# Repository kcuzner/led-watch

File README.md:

# LED Wristwatch

By Kevin Cuzner

## Design Features

- 32mm PCB diameter utilizing 72 0603 LEDs as the primary time display
    - Target is 3 square inches, 4 layer, with standard technology (6mil trace,
      no via in pad, etc)
- 100mAH battery from [PowerStream](http://www.powerstream.com/)
- Very high efficiency buck regulator.
    - Target battery life: >168 hours
- USB charging
- STM32L0-series microcontroller
- Side-actuated mid-board PCB mount buttons with an option for replacement with
  capacitive sensors.

## Key components

 - STM32L052C8 ultra-low power microcontroller
 - MMA8652 accelerometer
 - TPS65736 ultra-low quiescent current buck regulator
 - MCP73832 Li-Ion charge management controller

## Current status

This project is fairly complete, though the bootloader is still a work in
progress and may never be completed. The board was built and everything worked
after adding some reworks:

 - Trace to 3.3V from the SCL pullup was missing on the PCB. Apparently I
   deleted it while shuffling resistors around and didn't notice.
 - Central LED footprint was flipped across the X axis. The fix was to remove
   R35, short pins 1 and 4, and give up on having a blue LED in the center.
 - Leakage on Q1 through R4 (and D2, D1, and possibly U1) was enough to turn on
   the transistor. Changed R4 to 20K and bodged in a 4.7K resistor between Q1
   pins 1 and 2.

There were also two part issues which were resolved in software mostly:

 - The buttons I chose are extremely fragile. The mere act of inserting the PCB
   into the case put enough strain on them at times that 3 of the 4 buttons
   ended up breaking (they were constructed of a plastic housing with a metal
   dome held in place with what appears to be kapton tape). The buttons were
   simply not used in the software.
 - The blue LEDs I chose did not have a reverse current specification and in
   fact were not designed for reverse voltage operation. I didn't notice this
   when choosing parts, as I was rather focused on the forward voltage.
   Considering that reverse voltage is kind of key to the design here, that
   didn't work so well. Combined, the blue LEDs would draw about 28mA when the
   watch face was on or off because they actually conduct backwards. It could be
   said that they have an extremely high reverse leakage current, but I'm sure
   there's more going on there. The fix for this was to ensure that pin PA5,
   which drives the blue LEDs, was always high when the mux was disabled and all
   of its pins were driven high (effectively putting 0V across the LEDs). This
   does not reduce current consumption when the display is running (it still
   draws around 28mA), but it did reduce the sleep current to about 0.47mA.

Currently, the only method of input is either through USB or through the
accelerometer. The time is set through USB to the current time on the host PC.
The watch will automatically sleep when it is removed from USB power and will
wake when the accelerometer is tapped. When the watch is awake, the current time
is displayed. It currently stays on for about 15 seconds until shutting off
again. When USB power is reapplied the watch will reawaken. The future plans are
to also enable USB programmability of the watch, though this may never be
completed depending on my schedule and level of interest. The buttons may never
be used because they are so easy to break, but the idea was to have it behave
like a real digital watch with a timer and everything. All it does with the
buttons right now is beep when they are pressed.

As this is my first complete hardware design that I am releasing like this, I do
reserve the right to take it down at any time. I'm releasing it in the hopes
that someone finds it useful, though it clearly has its own problems and
shouldn't be considered as a reference design.

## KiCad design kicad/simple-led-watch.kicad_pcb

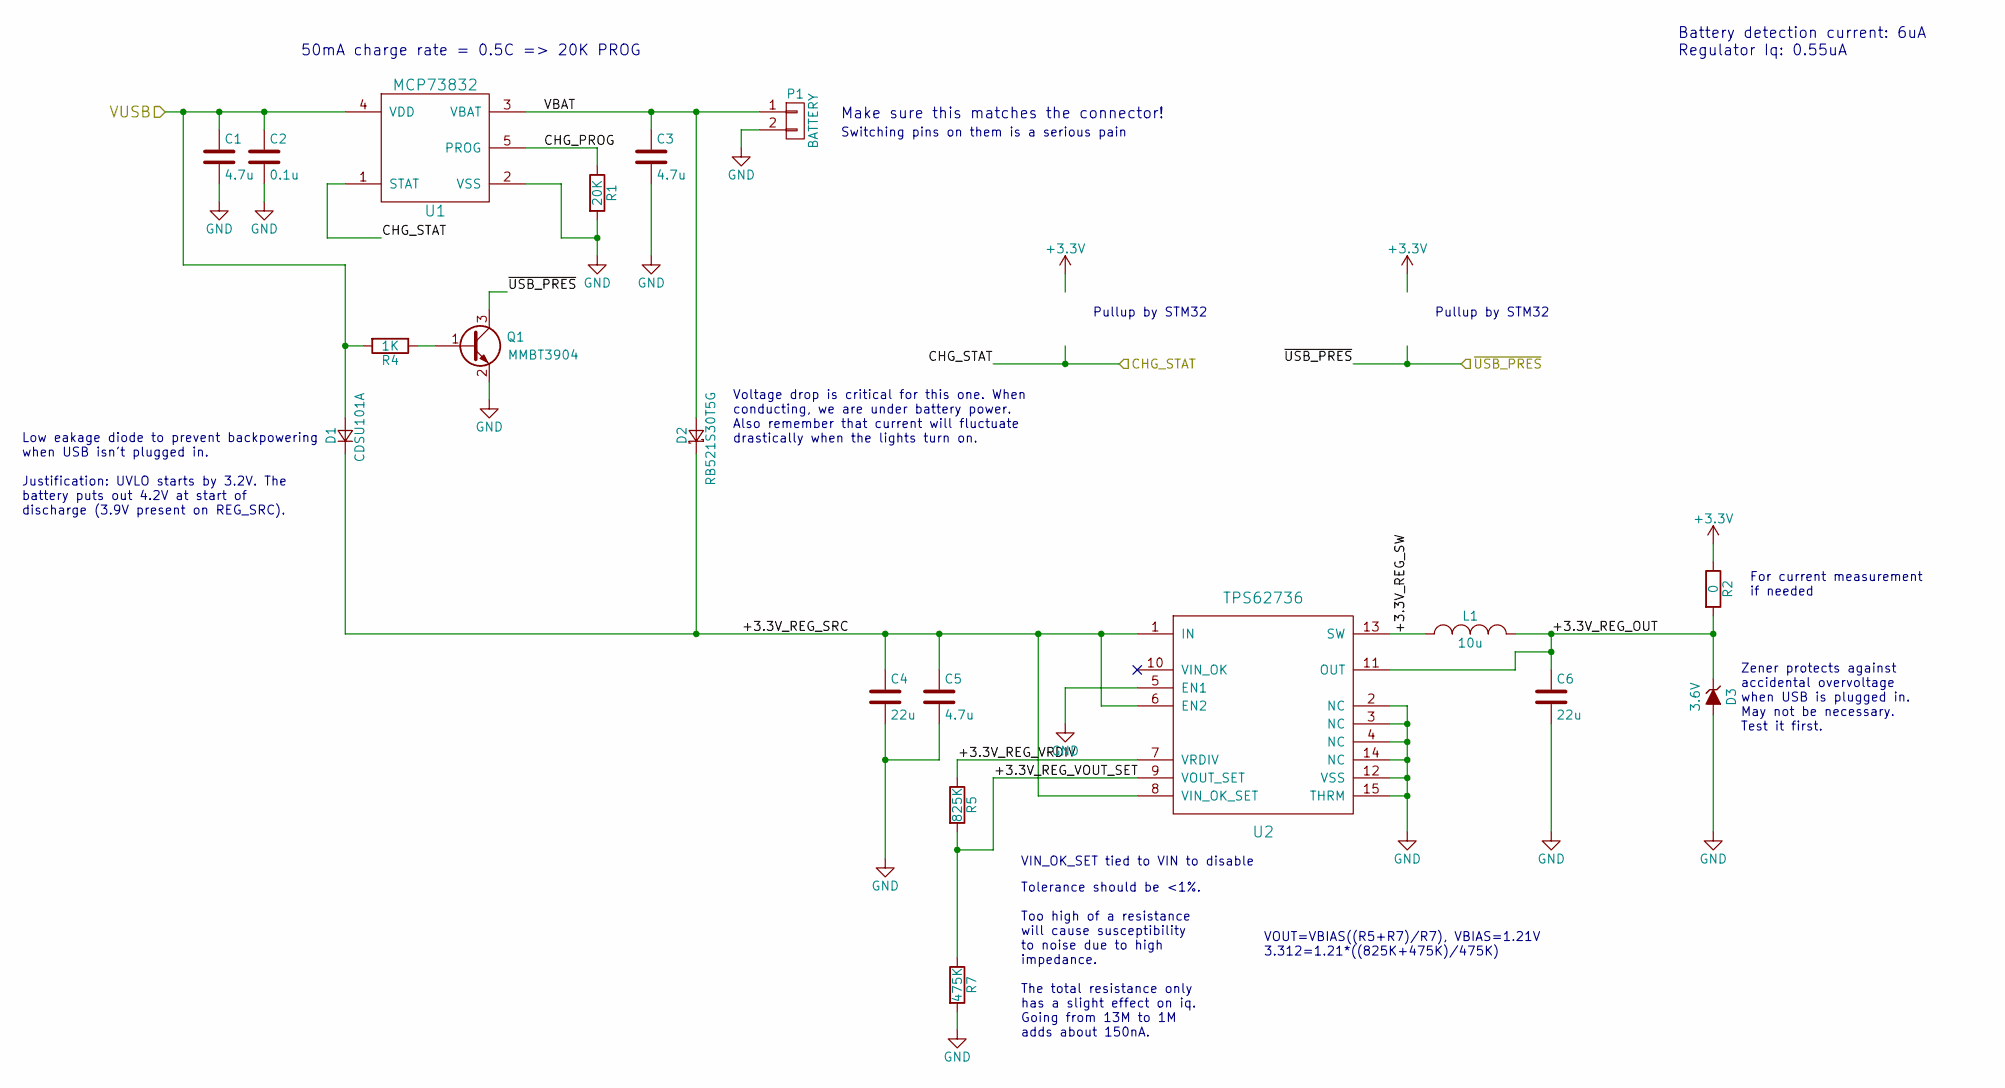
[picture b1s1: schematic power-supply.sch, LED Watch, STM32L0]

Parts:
C1, C3, C5: 4.7u; C_0402; Part No. 1276-6819-1-ND
C2: 0.1u; C_0402; Part No. 1276-1022-1-ND
C4, C6: 22u; C_0603; Part No. 1276-6504-1-ND
D1: CDSU101A; SOD-523; Part No. 641-1002-1-ND
D2: RB521S30T5G; SOD-523; Part No. RB521S30T5GOSCT-ND
D3: 3.6V; SOD-523; Part No. DZ2S036M0LCT-ND
L1: 10u; SMD_1008; Part No. 490-10563-1-ND
P1: BATTERY; JST-ACH-2PIN; Part No. 455-2202-1-ND
Q1: MMBT3904; SOT-23; Part No. MMBT3904FSCT-ND
R1: 20K; R_0402; Part No. 311-20.0KLRCT-ND
R2: 0; R_0402; Part No. 311-0.0JRCT-ND
R4: 1K; R_0402; Part No. 311-1.00KLRCT-ND
R5: 825K; R_0402; Part No. YAG3241CT-ND
R7: 475K; R_0402; Part No. 311-475KLRCT-ND
U1: MCP73832; SOT-23-5; Part No. MCP73832T-2DCI/OTCT-ND
U2: TPS62736; 14-VQFN; Part No. 296-43622-1-ND

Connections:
+3V3: R2.1; also elsewhere on the board
/Control/CHG_STAT: U1.1 (STAT); also elsewhere on the board
/Control/~USB_PRES: Q1.3 (C); also elsewhere on the board
/Power Supply/+3.3V_REG_OUT: C6.1, D3.1 (K), L1.2, R2.2, U2.11 (OUT)
/Power Supply/+3.3V_REG_SRC: C4.1, C5.1, D1.1 (K), D2.1 (K), U2.1 (IN), U2.6 (EN2), U2.8 (VIN_OK_SET)
/Power Supply/+3.3V_REG_SW: L1.1, U2.13 (SW)
/Power Supply/+3.3V_REG_VOUT_SET: R5.2, R7.1, U2.9 (VOUT_SET)
/Power Supply/+3.3V_REG_VRDIV: R5.1, U2.7 (VRDIV)
/Power Supply/CHG_PROG: R1.1, U1.5 (PROG)
/Power Supply/VBAT: C3.1, D2.2 (A), P1.1, U1.3 (VBAT)
/Power Supply/VUSB: C1.1, C2.1, D1.2 (A), R4.2, U1.4 (VDD); also elsewhere on the board
GND: C1.2, C2.2, C3.2, C4.2, C5.2, C6.2, D3.2 (A), P1.2, Q1.2 (E), R1.2, R7.2, U1.2 (VSS), U2.2 (NC), U2.3 (NC), U2.4 (NC), U2.5 (EN1), U2.12 (VSS), U2.14 (NC), U2.15 (THRM); also elsewhere on the board
unnamed: Q1.1 (B), R4.1

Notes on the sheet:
50mA charge rate = 0.5C => 20K PROG
Make sure this matches the connector!
Switching pins on them is a serious pain
Battery detection current: 6uA Regulator Iq: 0.55uA
Low eakage diode to prevent backpowering when USB isn't plugged in. Justification: UVLO starts by 3.2V. The battery puts out 4.2V at start of discharge (3.9V present on REG_SRC).
Voltage drop is critical for this one. When conducting, we are under battery power. Also remember that current will fluctuate drastically when the lights turn on.
Pullup by STM32
For current measurement if needed
Zener protects against accidental overvoltage when USB is plugged in. May not be necessary. Test it first.
VIN_OK_SET tied to VIN to disable
Tolerance should be <1%. Too high of a resistance will cause susceptibility to noise due to high impedance. The total resistance only has a slight effect on iq. Going from 13M to 1M adds about 150nA.
VOUT=VBIAS((R5+R7)/R7), VBIAS=1.21V 3.312=1.21*((825K+475K)/475K)

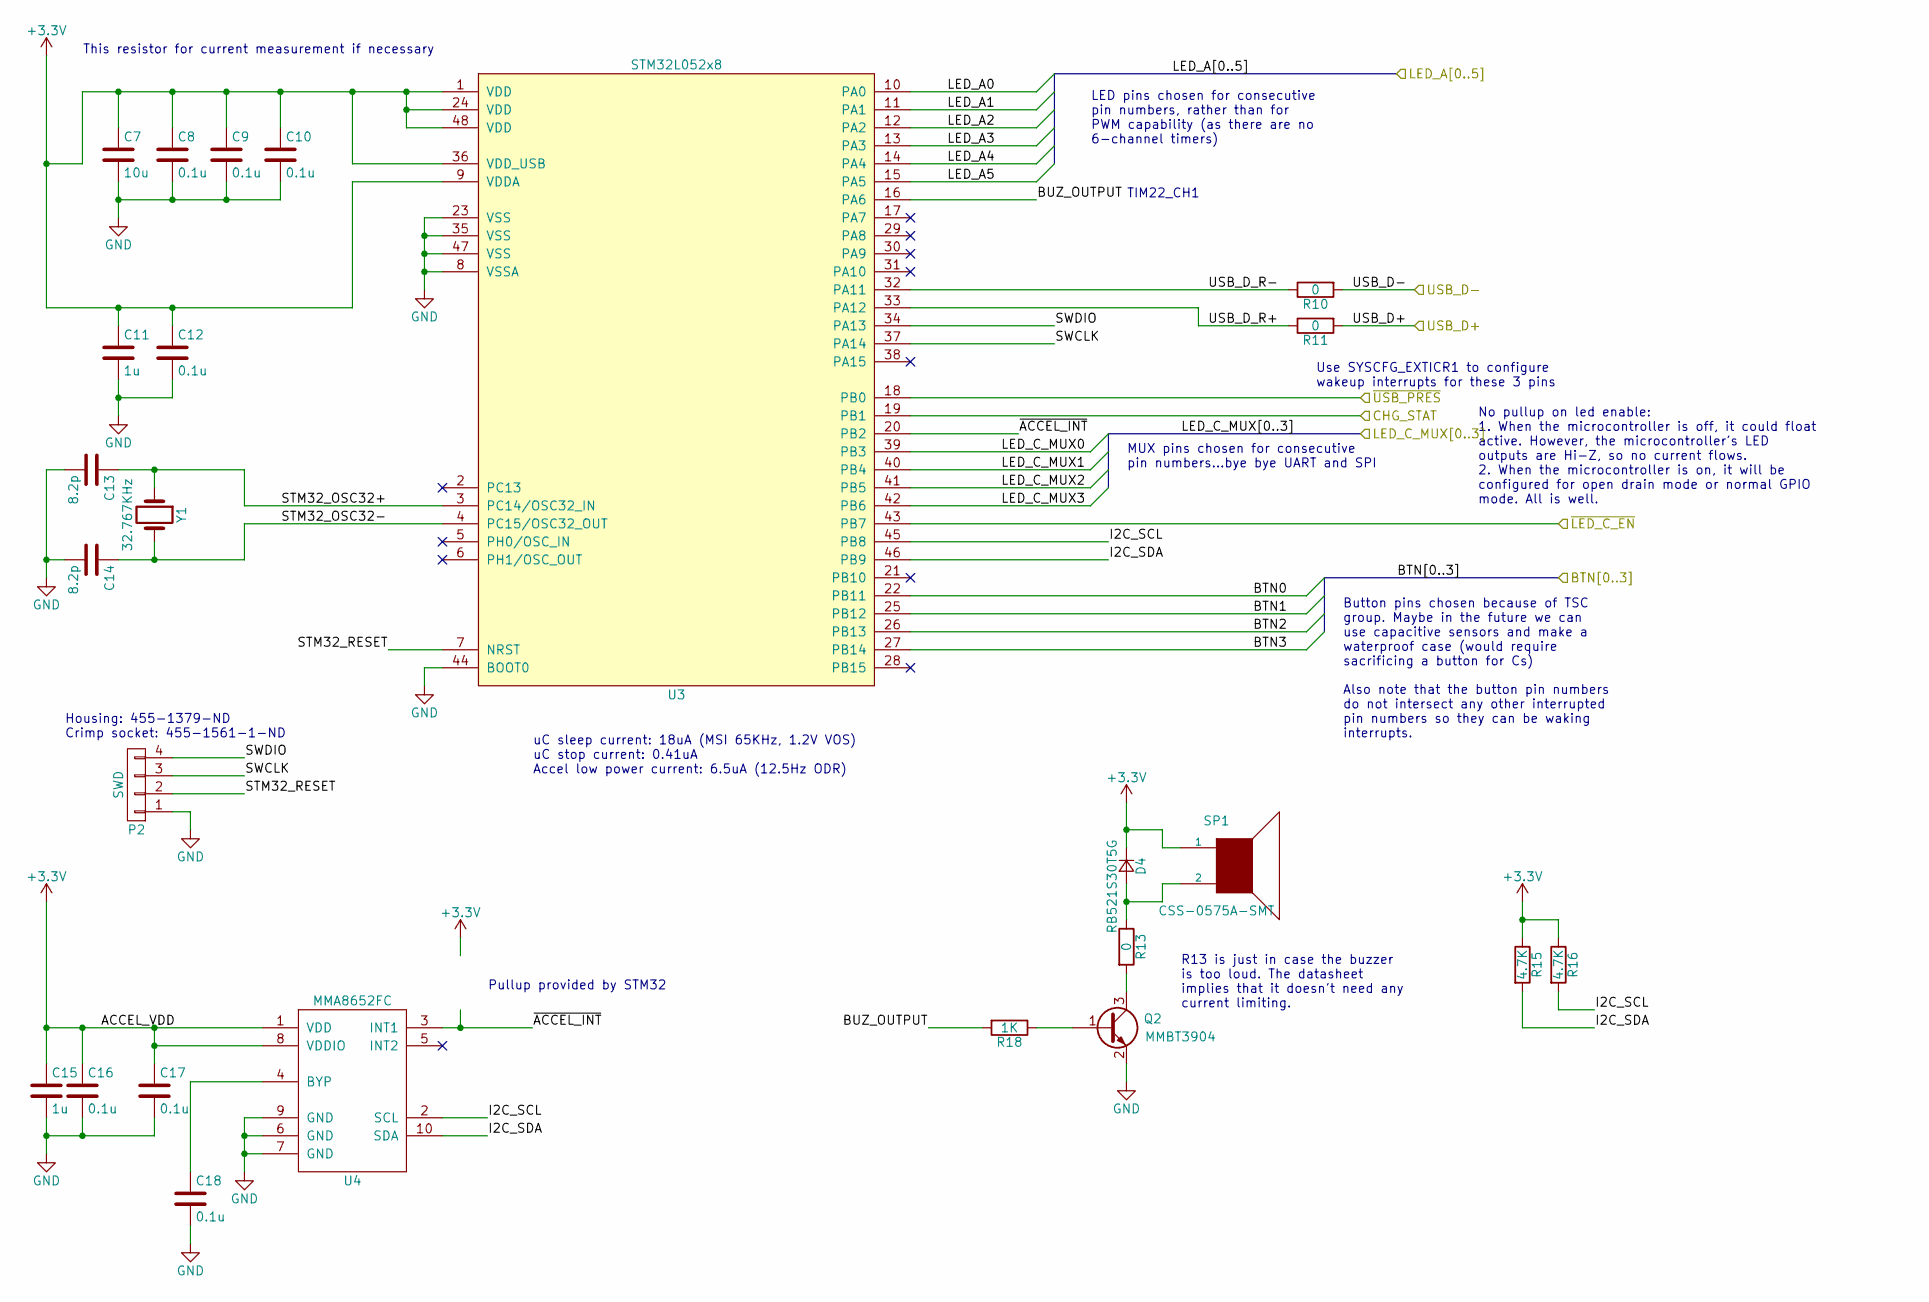
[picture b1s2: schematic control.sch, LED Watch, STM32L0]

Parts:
C7: 10u; C_0402; Part No. 1276-6830-1-ND
C8, C9, C10, C12, C16, C17, C18: 0.1u; C_0402; Part No. 1276-1022-1-ND
C11, C15: 1u; C_0402; Part No. 1276-1448-1-ND
C13, C14: 8.2p; C_0402; Part No. 490-6256-1-ND
D4: RB521S30T5G; SOD-523; Part No. RB521S30T5GOSCT-ND
P2: SWD; JST-SH-4; Part No. 455-1790-1-ND
Q2: MMBT3904; SOT-23; Part No. MMBT3904FSCT-ND
R10, R11, R13: 0; R_0402; Part No. 311-0.0JRCT-ND
R15, R16: 4.7K; R_0402; Part No. 311-4.7KLRCT-ND
R18: 1K; R_0402; Part No. 311-10.0KLRCT-ND
SP1: CSS-0575A-SMT; Part No. 102-2201-1-ND
U3: STM32L052x8; LQFP-48_7x7mm_Pitch0.5mm; Part No. 497-14903-ND
U4: MMA8652FC; 10-DFN; Part No. MMA8652FCR1CT-ND
Y1: 32.767KHz; Crystal-Abracon-ABS07; Part No. 535-11937-1-ND

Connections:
+3V3: C7.1, C8.1, C9.1, C10.1, C11.1, C12.1, C15.1, C16.1, C17.1, D4.1 (K), R15.1, R16.1, SP1.1, U3.1 (VDD), U3.9 (VDDA), U3.24 (VDD), U3.36 (VDD_USB), U3.48 (VDD), U4.1 (VDD), U4.8 (VDDIO); also elsewhere on the board
/Control/BTN0: U3.22 (PB11); also elsewhere on the board
/Control/BTN1: U3.25 (PB12); also elsewhere on the board
/Control/BTN2: U3.26 (PB13); also elsewhere on the board
/Control/BTN3: U3.27 (PB14); also elsewhere on the board
/Control/BUZ_OUTPUT: R18.2, U3.16 (PA6)
/Control/CHG_STAT: U3.19 (PB1); also elsewhere on the board
/Control/I2C_SCL: R16.2, U3.45 (PB8), U4.2 (SCL)
/Control/I2C_SDA: R15.2, U3.46 (PB9), U4.10 (SDA)
/Control/LED_A0: U3.10 (PA0); also elsewhere on the board
/Control/LED_A1: U3.11 (PA1); also elsewhere on the board
/Control/LED_A2: U3.12 (PA2); also elsewhere on the board
/Control/LED_A3: U3.13 (PA3); also elsewhere on the board
/Control/LED_A4: U3.14 (PA4); also elsewhere on the board
/Control/LED_A5: U3.15 (PA5); also elsewhere on the board
/Control/LED_C_MUX0: U3.39 (PB3); also elsewhere on the board
/Control/LED_C_MUX1: U3.40 (PB4); also elsewhere on the board
/Control/LED_C_MUX2: U3.41 (PB5); also elsewhere on the board
/Control/LED_C_MUX3: U3.42 (PB6); also elsewhere on the board
/Control/STM32_OSC32+: C13.1, U3.3 (PC14/OSC32_IN), Y1.1
/Control/STM32_OSC32-: C14.1, U3.4 (PC15/OSC32_OUT), Y1.2
/Control/STM32_RESET: P2.2, U3.7 (NRST)
/Control/SWCLK: P2.3, U3.37 (PA14)
/Control/SWDIO: P2.4, U3.34 (PA13)
/Control/USB_D+: R11.2; also elsewhere on the board
/Control/USB_D-: R10.2; also elsewhere on the board
/Control/USB_D_R+: R11.1, U3.33 (PA12)
/Control/USB_D_R-: R10.1, U3.32 (PA11)
/Control/~ACCEL_INT: U3.20 (PB2), U4.3 (INT1)
/Control/~LED_C_EN: U3.43 (PB7); also elsewhere on the board
/Control/~USB_PRES: U3.18 (PB0); also elsewhere on the board
GND: C7.2, C8.2, C9.2, C10.2, C11.2, C12.2, C13.2, C14.2, C15.2, C16.2, C17.2, C18.2, P2.1, Q2.2 (E), U3.8 (VSSA), U3.23 (VSS), U3.35 (VSS), U3.44 (BOOT0), U3.47 (VSS), U4.6 (GND), U4.7 (GND), U4.9 (GND); also elsewhere on the board
unnamed: C18.1, U4.4 (BYP)
unnamed: D4.2 (A), R13.1, SP1.2
unnamed: Q2.1 (B), R18.1
unnamed: Q2.3 (C), R13.2

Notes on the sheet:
This resistor for current measurement if necessary
LED pins chosen for consecutive pin numbers, rather than for PWM capability (as there are no 6-channel timers)
uC sleep current: 18uA (MSI 65KHz, 1.2V VOS) uC stop current: 0.41uA Accel low power current: 6.5uA (12.5Hz ODR)
MUX pins chosen for consecutive pin numbers...bye bye UART and SPI
Button pins chosen because of TSC group. Maybe in the future we can use capacitive sensors and make a waterproof case (would require sacrificing a button for Cs)
Use SYSCFG_EXTICR1 to configure wakeup interrupts for these 3 pins
TIM22_CH1
Also note that the button pin numbers do not intersect any other interrupted pin numbers so they can be waking interrupts.
No pullup on led enable: 1. When the microcontroller is off, it could float active. However, the microcontroller's LED outputs are Hi-Z, so no current flows. 2. When the microcontroller is on, it will be configured for open drain mode or normal GPIO mode. All is well.
Pullup provided by STM32
Housing: 455-1379-ND Crimp socket: 455-1561-1-ND
R13 is just in case the buzzer is too loud. The datasheet implies that it doesn't need any current limiting.

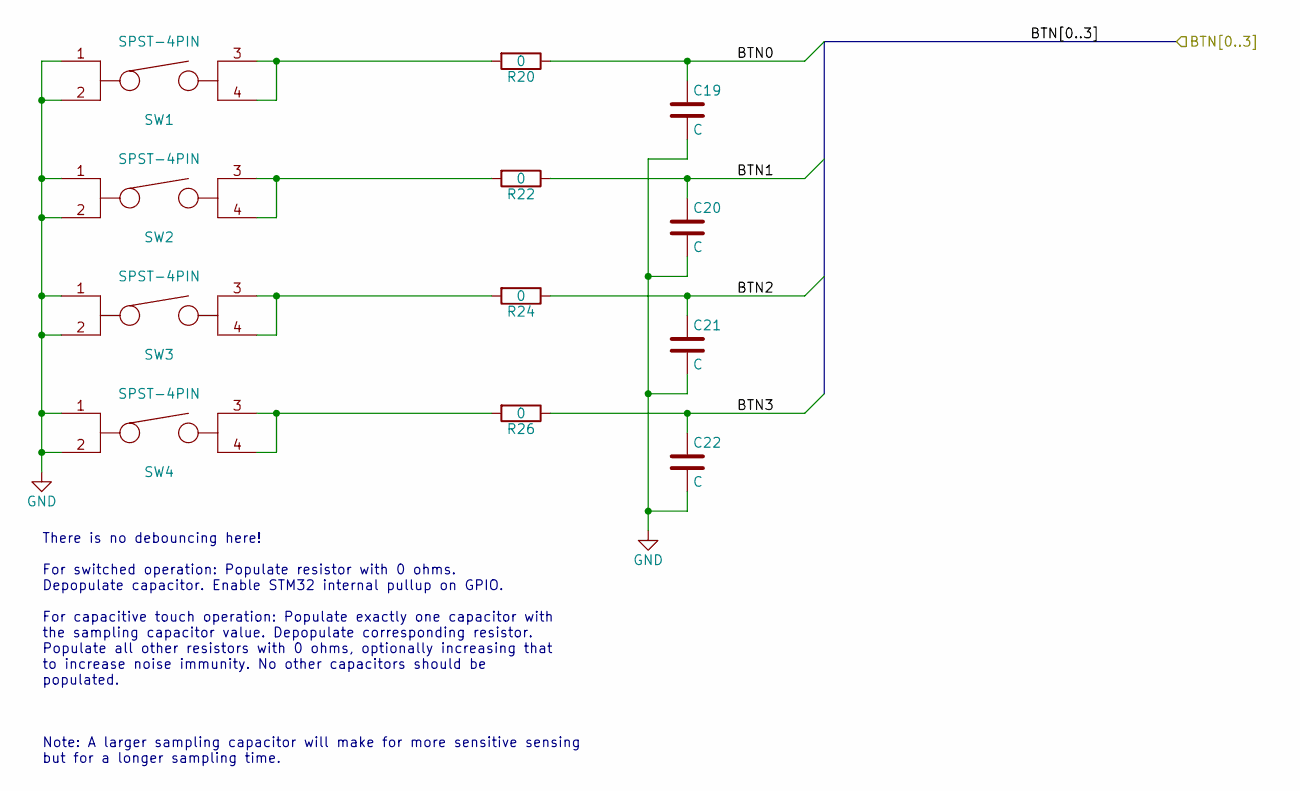
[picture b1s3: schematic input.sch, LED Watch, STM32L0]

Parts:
C19, C20, C21, C22: C; C_0402
R20, R22, R24, R26: 0; R_0402; Part No. 311-0.0JRCT-ND
SW1, SW2, SW3, SW4: SPST-4PIN; PAN-EVPAV; Part No. P16849CT-ND

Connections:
/Control/BTN0: C19.1, R20.1; also elsewhere on the board
/Control/BTN1: C20.1, R22.1; also elsewhere on the board
/Control/BTN2: C21.1, R24.1; also elsewhere on the board
/Control/BTN3: C22.1, R26.1; also elsewhere on the board
GND: C19.2, C20.2, C21.2, C22.2, SW1.1, SW1.2, SW2.1, SW2.2, SW3.1, SW3.2, SW4.1, SW4.2; also elsewhere on the board
unnamed: R20.2, SW1.3, SW1.4
unnamed: R22.2, SW2.3, SW2.4
unnamed: R24.2, SW3.3, SW3.4
unnamed: R26.2, SW4.3, SW4.4

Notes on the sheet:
Note: A larger sampling capacitor will make for more sensitive sensing but for a longer sampling time.
There is no debouncing here! For switched operation: Populate resistor with 0 ohms. Depopulate capacitor. Enable STM32 internal pullup on GPIO. For capacitive touch operation: Populate exactly one capacitor with the sampling capacitor value. Depopulate corresponding resistor. Populate all other res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

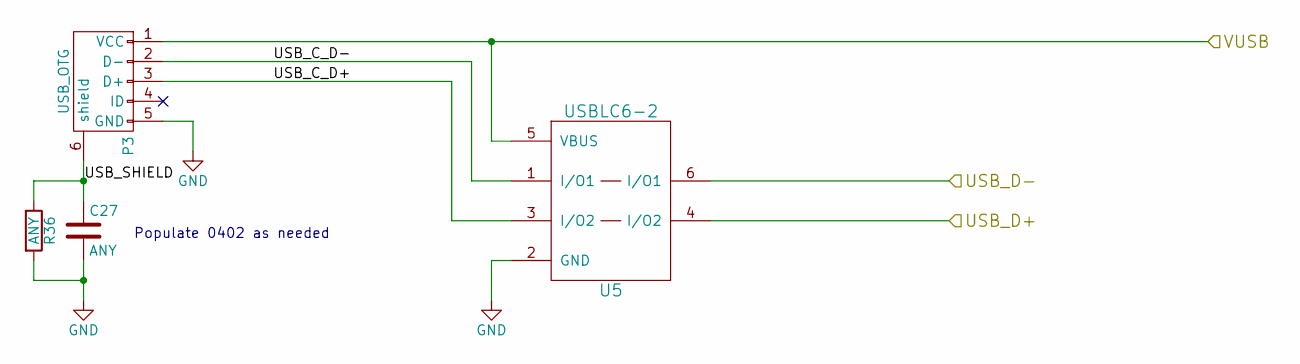
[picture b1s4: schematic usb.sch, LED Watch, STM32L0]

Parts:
C27: ANY; C_0402
P3: USB_OTG; AMP-10104110-USB; Part No. 609-4052-1-ND
R36: ANY; R_0402
U5: USBLC6-2; SOT-666; Part No. 497-5026-1-ND

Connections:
/Control/USB_D+: U5.4 (I/O2); also elsewhere on the board
/Control/USB_D-: U5.6 (I/O1); also elsewhere on the board
/Power Supply/VUSB: P3.1 (VCC), U5.5 (VBUS); also elsewhere on the board
/USB/USB_C_D+: P3.3 (D+), U5.3 (I/O2)
/USB/USB_C_D-: P3.2 (D-), U5.1 (I/O1)
/USB/USB_SHIELD: C27.1, P3.6 (shield), R36.1
GND: C27.2, P3.5 (GND), R36.2, U5.2 (GND); also elsewhere on the board

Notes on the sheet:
Populate 0402 as needed

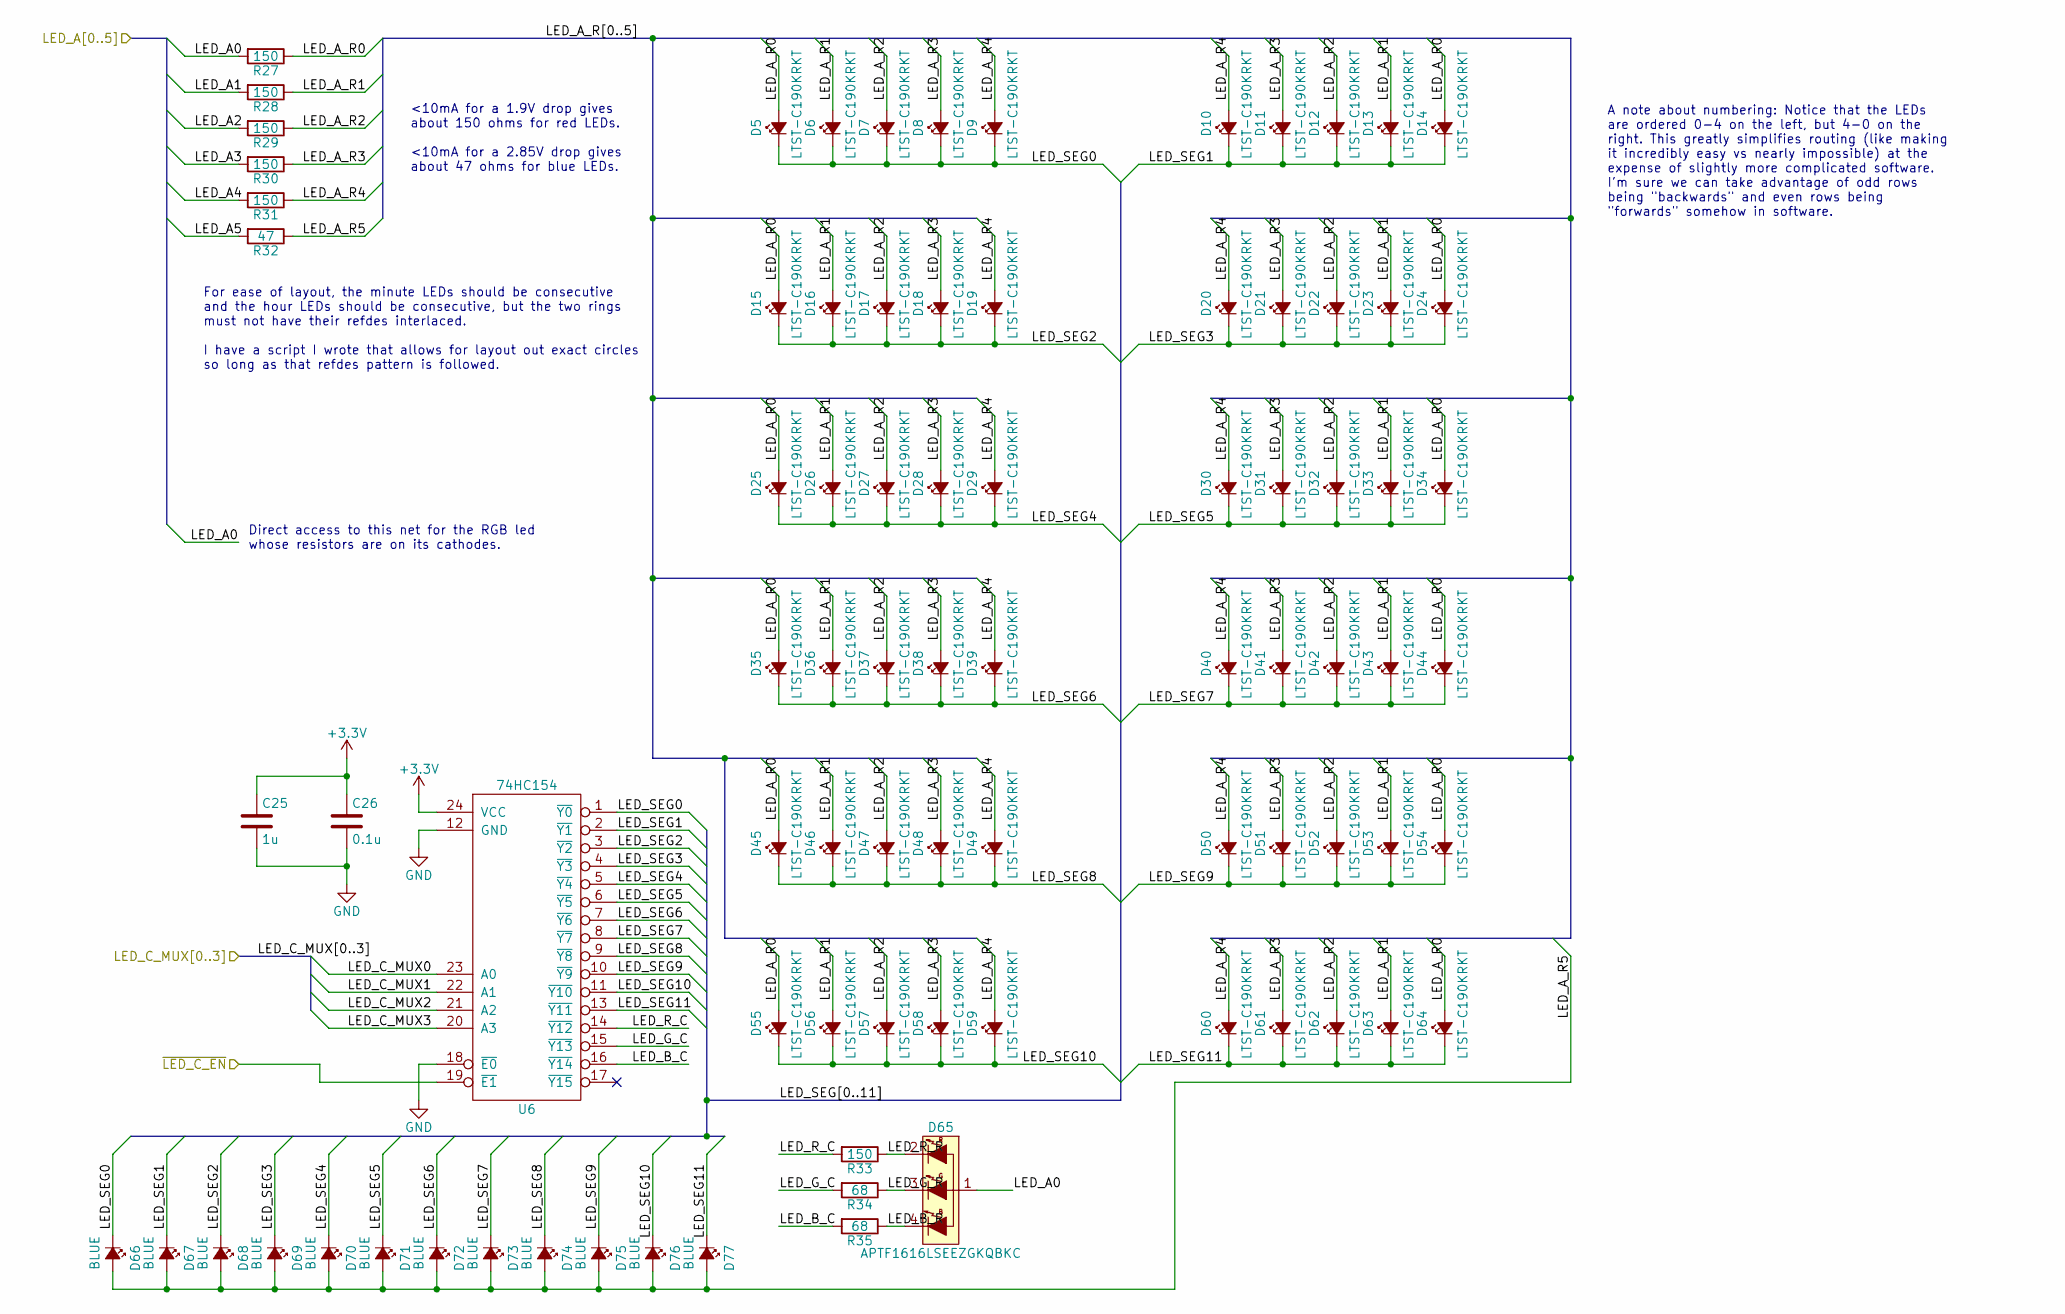
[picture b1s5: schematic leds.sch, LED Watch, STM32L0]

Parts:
C25: 1u; C_0402; Part No. 1276-1448-1-ND
C26: 0.1u; C_0402; Part No. 1276-1022-1-ND
D5, D6, D7, D8, D9, D10, D11, D12, D13, D14, D15, D16, D17, D18, D19, D20, D21, D22, D23, D24, D25, D26, D27, D28, D29, D30, D31, D32, D33, D34, D35, D36, D37, D38, D39, D40, D41, D42, D43, D44, D45, D46, D47, D48, D49, D50, D51, D52, D53, D54, D55, D56, D57, D58, D59, D60, D61, D62, D63, D64: LTST-C190KRKT; LED_0603; Part No. 160-1436-1-ND
D65: APTF1616LSEEZGKQBKC; LED-0606; Part No. 754-1972-1-ND
D66, D67, D68, D69, D70, D71, D72, D73, D74, D75, D76, D77: BLUE; LED_0603; Part No. 475-2815-1-ND
R27, R28, R29, R30, R31, R33: 150; R_0402; Part No. 311-150LRCT-ND
R32: 47; R_0402; Part No. 311-47.0LRCT-ND
R34, R35: 68; R_0402; Part No. 311-68.0LRCT-ND
U6: 74HC154; DHVQFN24; Part No. 568-8858-1-ND

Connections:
+3V3: C25.1, C26.1, U6.24 (VCC); also elsewhere on the board
/Control/LED_A0: D65.1, R27.2; also elsewhere on the board
/Control/LED_A1: R28.2; also elsewhere on the board
/Control/LED_A2: R29.2; also elsewhere on the board
/Control/LED_A3: R30.2; also elsewhere on the board
/Control/LED_A4: R31.2; also elsewhere on the board
/Control/LED_A5: R32.2; also elsewhere on the board
/Control/LED_C_MUX0: U6.23 (A0); also elsewhere on the board
/Control/LED_C_MUX1: U6.22 (A1); also elsewhere on the board
/Control/LED_C_MUX2: U6.21 (A2); also elsewhere on the board
/Control/LED_C_MUX3: U6.20 (A3); also elsewhere on the board
/Control/~LED_C_EN: U6.19 (~E1); also elsewhere on the board
/LEDs/LED_A_R0: D5.2 (A), D14.2 (A), D15.2 (A), D24.2 (A), D25.2 (A), D34.2 (A), D35.2 (A), D44.2 (A), D45.2 (A), D54.2 (A), D55.2 (A), D64.2 (A), R27.1
/LEDs/LED_A_R1: D6.2 (A), D13.2 (A), D16.2 (A), D23.2 (A), D26.2 (A), D33.2 (A), D36.2 (A), D43.2 (A), D46.2 (A), D53.2 (A), D56.2 (A), D63.2 (A), R28.1
/LEDs/LED_A_R2: D7.2 (A), D12.2 (A), D17.2 (A), D22.2 (A), D27.2 (A), D32.2 (A), D37.2 (A), D42.2 (A), D47.2 (A), D52.2 (A), D57.2 (A), D62.2 (A), R29.1
/LEDs/LED_A_R3: D8.2 (A), D11.2 (A), D18.2 (A), D21.2 (A), D28.2 (A), D31.2 (A), D38.2 (A), D41.2 (A), D48.2 (A), D51.2 (A), D58.2 (A), D61.2 (A), R30.1
/LEDs/LED_A_R4: D9.2 (A), D10.2 (A), D19.2 (A), D20.2 (A), D29.2 (A), D30.2 (A), D39.2 (A), D40.2 (A), D49.2 (A), D50.2 (A), D59.2 (A), D60.2 (A), R31.1
/LEDs/LED_A_R5: D66.2 (A), D67.2 (A), D68.2 (A), D69.2 (A), D70.2 (A), D71.2 (A), D72.2 (A), D73.2 (A), D74.2 (A), D75.2 (A), D76.2 (A), D77.2 (A), R32.1
/LEDs/LED_B_C: R35.2, U6.16 (~Y14)
/LEDs/LED_B_R: D65.4 (B), R35.1
/LEDs/LED_G_C: R34.2, U6.15 (~Y13)
/LEDs/LED_G_R: D65.3 (G), R34.1
/LEDs/LED_R_C: R33.2, U6.14 (~Y12)
/LEDs/LED_R_R: D65.2 (R), R33.1
/LEDs/LED_SEG0: D5.1 (K), D6.1 (K), D7.1 (K), D8.1 (K), D9.1 (K), D66.1 (K), U6.1 (~Y0)
/LEDs/LED_SEG1: D10.1 (K), D11.1 (K), D12.1 (K), D13.1 (K), D14.1 (K), D67.1 (K), U6.2 (~Y1)
/LEDs/LED_SEG2: D15.1 (K), D16.1 (K), D17.1 (K), D18.1 (K), D19.1 (K), D68.1 (K), U6.3 (~Y2)
/LEDs/LED_SEG3: D20.1 (K), D21.1 (K), D22.1 (K), D23.1 (K), D24.1 (K), D69.1 (K), U6.4 (~Y3)
/LEDs/LED_SEG4: D25.1 (K), D26.1 (K), D27.1 (K), D28.1 (K), D29.1 (K), D70.1 (K), U6.5 (~Y4)
/LEDs/LED_SEG5: D30.1 (K), D31.1 (K), D32.1 (K), D33.1 (K), D34.1 (K), D71.1 (K), U6.6 (~Y5)
/LEDs/LED_SEG6: D35.1 (K), D36.1 (K), D37.1 (K), D38.1 (K), D39.1 (K), D72.1 (K), U6.7 (~Y6)
/LEDs/LED_SEG7: D40.1 (K), D41.1 (K), D42.1 (K), D43.1 (K), D44.1 (K), D73.1 (K), U6.8 (~Y7)
/LEDs/LED_SEG8: D45.1 (K), D46.1 (K), D47.1 (K), D48.1 (K), D49.1 (K), D74.1 (K), U6.9 (~Y8)
/LEDs/LED_SEG9: D50.1 (K), D51.1 (K), D52.1 (K), D53.1 (K), D54.1 (K), D75.1 (K), U6.10 (~Y9)
/LEDs/LED_SEG10: D55.1 (K), D56.1 (K), D57.1 (K), D58.1 (K), D59.1 (K), D76.1 (K), U6.11 (~Y10)
/LEDs/LED_SEG11: D60.1 (K), D61.1 (K), D62.1 (K), D63.1 (K), D64.1 (K), D77.1 (K), U6.13 (~Y11)
GND: C25.2, C26.2, U6.12 (GND), U6.18 (~E0); also elsewhere on the board

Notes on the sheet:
For ease of layout, the minute LEDs should be consecutive and the hour LEDs should be consecutive, but the two rings must not have their refdes interlaced. I have a script I wrote that allows for layout out exact circles so long as that refdes pattern is followed.
A note about numbering: Notice that the LEDs are ordered 0-4 on the left, but 4-0 on the right. This greatly simplifies routing (like making it incredibly easy vs nearly impossible) at the expense of slightly more complicated software. I'm sure we can take advantage of odd rows being "backwards" an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
Direct access to this net for the RGB led whose resistors are on its cathodes.
<10mA for a 1.9V drop gives about 150 ohms for red LEDs. <10mA for a 2.85V drop gives about 47 ohms for blue LEDs.

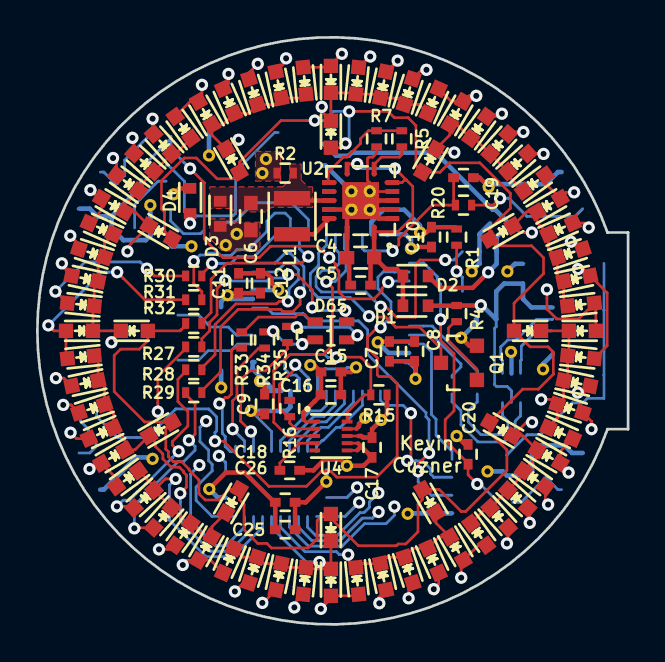
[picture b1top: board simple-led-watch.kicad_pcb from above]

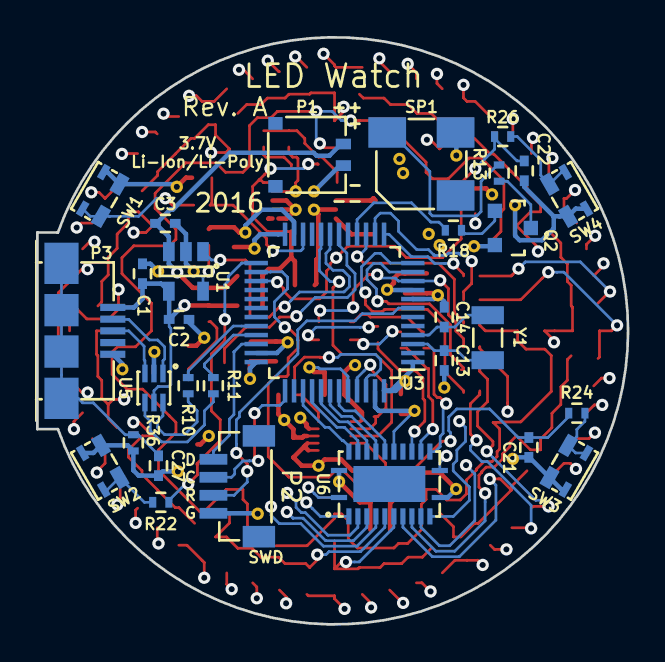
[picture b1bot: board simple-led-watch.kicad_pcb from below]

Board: 4 copper layers, 32.8 x 32.6 mm, 145 parts (30 on the bottom side), 76 nets.

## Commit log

2016-10-16 Added footprints for most major components
    We are missing almost all passives
2016-10-17 Completed initial placement of major components
    The passives are causing trouble. We need to eliminate every pullup
    possible.
2016-10-17 Finished initial placement of all components
    Got rid of several pullup resistors and unnecessary components.
2016-10-18 Initial route of power and LED ring
    I had to do the order swapping thing that I did on the last design
2016-10-18 Routed most of the board, except buttons and interrupts
2016-10-19 Selected programming header
    Only one non-connected trace left. And I don't know where it is...
2016-10-19 Added license
2016-10-20 Placed parts for round two
    I'm pretty sure I can do it better
2016-10-21 Finished round two routing
    This layout cuts through the middle of no planes and has more
    predictable power paths (without needing Hyperlynx or something like
    that). It also routes all signals but the LED-related ones on just the
    top and bottom layers, as it is meant to be. It also nearly comforms to
    the recommended layout for the regulator. There also aren't any ICs
    without a full reference plane beneath them.
2016-10-21 Fixed silkscreen and added markings
2016-10-22 Added 3D models for most large parts
2016-12-03 Added more 3D models for tall parts
2016-12-05 Changed out D65 RGB LED for a shorter 0606 part
2016-12-20 Adding initial case model
2016-12-21 Changed case to a two-piece snapping design
    Results:
    - After adding a serious chamfer on the bottom of the lid, the pieces
    "snapped" together...by acting as a lever on the tabs on the bottom
    piece and breaking them off. The clips on the tabs are too big (0.5mm).
    - Tolerances are very tight on the vertical sections. The circular
    tolerances between the lid and bottom are good. This contributed to the
2017-01-14 Upgrade to latest kicad, add some measurements
2017-01-14 Checked layout and reference designs, swapped crystal and RGB LED
    ST has a list of suggested crystals which are known to work with the
    STM32L0 family. I selected one of those and it is significantly
    smaller in all dimensions.
    The RGB LED had too high of a green voltage. I swapped it out for a
    slightly more expensive one with the same footprint that had startlingly
    low green and blue forward voltages.
2017-01-14 Made some modifications to solder mask and traces for oshpark
2017-01-15 Added date and revision to schematic and layout
2017-01-29 Fixed solder paste mask over the DHVQFN24
2017-01-29 Added intial firmware with LED test
    The test is simple: Light up every LED.
    Turns out, that doesn't quite work. The 74HC154 raises the voltage at
    its outputs as current is sunk into them, so the blue LEDs don't
    illuminate very strongly (the center blue LED doesn't illuminate visibly
    at all). This may be a problem, but we don't really intend to have more
    than two LEDs per segment illuminated.
2017-01-30 Added initial buzzer and button control firmware
2017-01-31 Added initial LED driver
    The test program makes a fun counting ring. I definitely did not count
    on the output resistance of the 74HC154 causing the blue LED to become
    marginally turned on when 4-5 red LEDs are lit. Very interesting.
2017-02-02 Fixed LED ISR and buzzer duty cycle voltage droop
    LED ISR: I forgot to reset the status register, so it would continuously
    execute. I also found that I needed to up the refresh rate by a lot to
    remove visible flicker. I suspect this stems from the fact that all
    segments are blanked except the one currently being illuminated.
    Buzzer duty cycle: The buzzer at 50% draws ~100mA average, with ~200mA
    peak, according to the datasheet. On the voltage rail, there is an
2017-02-02 Changed to newlib nano, fixing excessive .data usage
2017-02-02 Added initial I2C peripheral driver
    It does simple read-only or write-only transactions. This should be
    enough to operate the accelerometer.
2017-02-04 Added initial accelerometer code with pulse detection
2017-02-06 Added initial USB code without endpoint 0 handling
    The STM32L0 does the PMA just a tad differently than the STM32F1. The
    device can receive commands now.
2017-02-10 Added descriptor entry structure and implemented endp0 as state machine
    The state machine version is far easier to modify, meshes well with the
    hook system I've been implementing, and is very very easy to read.
2017-02-13 Tweaked setup state machine and packet handling. Device now enumerates.
2017-02-17 Implemented initial HID with simple report and rudimentary host software
    Trying to get the computer to poll it...so far its not happening, though
    it does create a /dev/hidraw for it.
2017-02-17 Fixed endpointa address and Linux will now poll the device
    Linux only starts polling the device once the device is opened. I wonder
    if Windows has similar behavior?
2017-02-20 Started adding host software structure
    Going to put this on hold for now since I'm actually not sure what I
    want it to do...
2017-02-25 Added initial RTC implementation
2017-02-25 Saving debug main program, with hard fault handler
    The hard fault handler is quite useful. It was borrowed from various
    places, including the FreeRTOS site and some Keil page.
2017-02-26 Added initial battery charge & usb detection, required bodge
    The bodge was adding a 4.7K resistor between the base and emitter of Q1
    and changing R4 to be 20K. The issue is that *something* is leaking 2V
    onto the 5V line, which is enough to turn on Q1 through a 10K resistor.
    I suspect the battery charger, but I guess it could be the diode I
    specifically selected for a low leakage current. In any case, the
    20K/4.7K voltage divider prevents the transistor from turning on until
2017-02-27 Added time setting capability from host software
2017-03-04 Added initial power management state machine, with stop mode
    It behaves like its in stop mode...so hopefully its in stop mode.
2017-03-04 Added initial clock speed management with callbacks
    It does actually seem to work. When the USB is disconnected, changing
    the MSI range really has a crazy effect on the display. Reconnecting the
    USB makes the artifacts disappear. All the while, the buzzer sounds the
    same frequency. I think it works.
2017-03-20 Added solder paste stencil blender file
2017-03-20 Initial case SCAD, with PCB
2017-03-21 Added additional cutouts to case
    A blank PCB fits perfectly. However, there is very little room for
    wiring the battery. The programming header is getting in the way and the
    wires also seem to be weakening, so I may need to replace the connector.
    This case version does not have the button slots.
2017-03-29 Added button cutouts to case with space for button caps
2017-03-30 Made a minor outside diameter change to remove a void around USB
    This is why doing this in OpenSCAD is great
2017-03-30 Created initial bootloader structure based on the firmware
    The linker script is not yet modified to relocate everything to RAM
2017-04-02 Added initial bootloader desription
2017-04-02 Expanded on bootloader description, changed bootloader to be in flash
    The bootloader is now truly a bootloader. Hooray.
2017-04-08 Added lid to case, shortened lid, added spring bar holes
    The battery compartment wasn't quite deep enough for the buzzer.
2017-04-08 Removed freecad version of case since we will be sticking with openscad
2017-04-10 Added lip to case and adjusted programming header height
    Making the lid just a touch larger moved the programming header in range
    of the connector.
2017-04-10 Increased the on-time of the watch
2017-04-15 Started modifying usb hid for bootloader 64-byte buffers
2017-04-15 Added case+PCB art blender file
2017-04-15 Fixed excessive sleep current consumption originating in the blue LEDs
    Turns out, the blue LEDs don't have a reverse current specification and
    they weren't designed to operate under reverse voltage. I missed that
    little tidbit in the datasheet and now I know what they do when reverse
    voltaged: They draw collectively 28mA or so through the microcontroller,
    even when sleeping. The reason is that since the mux is disabled and the
    hour pin is most likely set low (unless it happened to turn off when
2017-04-15 Widened the button holes further
2017-04-16 Updating readme and adding photo of finished watch
2017-04-18 Fixed usb implementation to allow overriding ZLP production
    Apparently the HID class does not use ZLPs. I *think* this should still
    be ok in the case of a report longer than the endpoint size and a
    multiple of the endpoint size since we already implement multi-transfer
    packetizing of buffers and that functionality still remains.
2017-04-19 Fixed problems with NOZLP and specific packet sizes
    In the event that a packet size was a multiple of the endpoint size, the
    device would be unable to send or receive more than the first <endpoint
    size> bytes. Additional logic was added to ensure that transfers are
    only completed once the expected number of bytes were sent or received.
    This still adds some additional peril for receivers which expect packets
    longer than the endpoint size since it will no longer complete a receive
2017-04-19 Updated HID firmware and changed host to python
2017-04-20 Merged firmware and bootloader common source and headers
2017-04-27 Added initial NVM writing functions and simple test
2017-04-27 Removed flash write test
    Every time we reset the chip it would do a flash write
2017-04-28 Added initial repeating status report logic to bootloader
2017-05-05 Created programming state machine and host hex loader
    Still working out some bugs with the CRCs
2017-05-08 Fixed CRC32 implementation, device now appears to be programmable!
2017-05-08 Increased poll rate to maximum and added progress bar to polling script
    I believe that the data rate is being limited by the handshaking that
    happens by enforcing a status report to be sent after every page
    command. However, this does allow us to stop programming and determine
    which page caused the error. Perhaps I need to rethink the status
    reports so that I can remove the ordering dependency.
2017-05-10 Added bootloader reset/entry and program start logic
    The device can now be programmed entirely over USB, provided that the
    user program implements some way to soft-reset the device.
2017-05-10 Modified firmware Makefile to use the bootloader for installation
2017-05-14 Added bootloader instructions and abort command
2022-12-25 Update usb.c
    If we try to optimize the code the USB will not be recognized, except -O0.
    I find that we need to keep the usb_handle_endp0 function in usb.c to O0 to avoid being optimized and then we can optimize the others.
    BR CCTSAO
